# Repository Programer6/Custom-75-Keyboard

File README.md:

# Wireless 75% Keyboard

This is the documentation for  designed completely from scratch.

For the firmware, I chose ZMK. Since this is a wireless build using the `nice!nano`, ZMK's powerful features and Bluetooth support were a perfect fit, even if it meant a steeper learning curve than like KMK which I have used before.

# Hardware Features
- 74-key, 70% layout with a function row.
- Wireless Bluetooth connectivity via a `nice!nano` microcontroller.
- `MCP23017` I/O expander to simplify wiring and save controller pins.
- 1x Rotary Encoder for volume or scrolling.
- Onboard potentiometer for screen brightness adjustment.
- Powered by a LiPo battery.

## Images

| Schematic  |
| :---: |
| |
|  |

| PCB Layout |
| :---: |
|  |

| 3D Case Design |
| :---: |
|  |

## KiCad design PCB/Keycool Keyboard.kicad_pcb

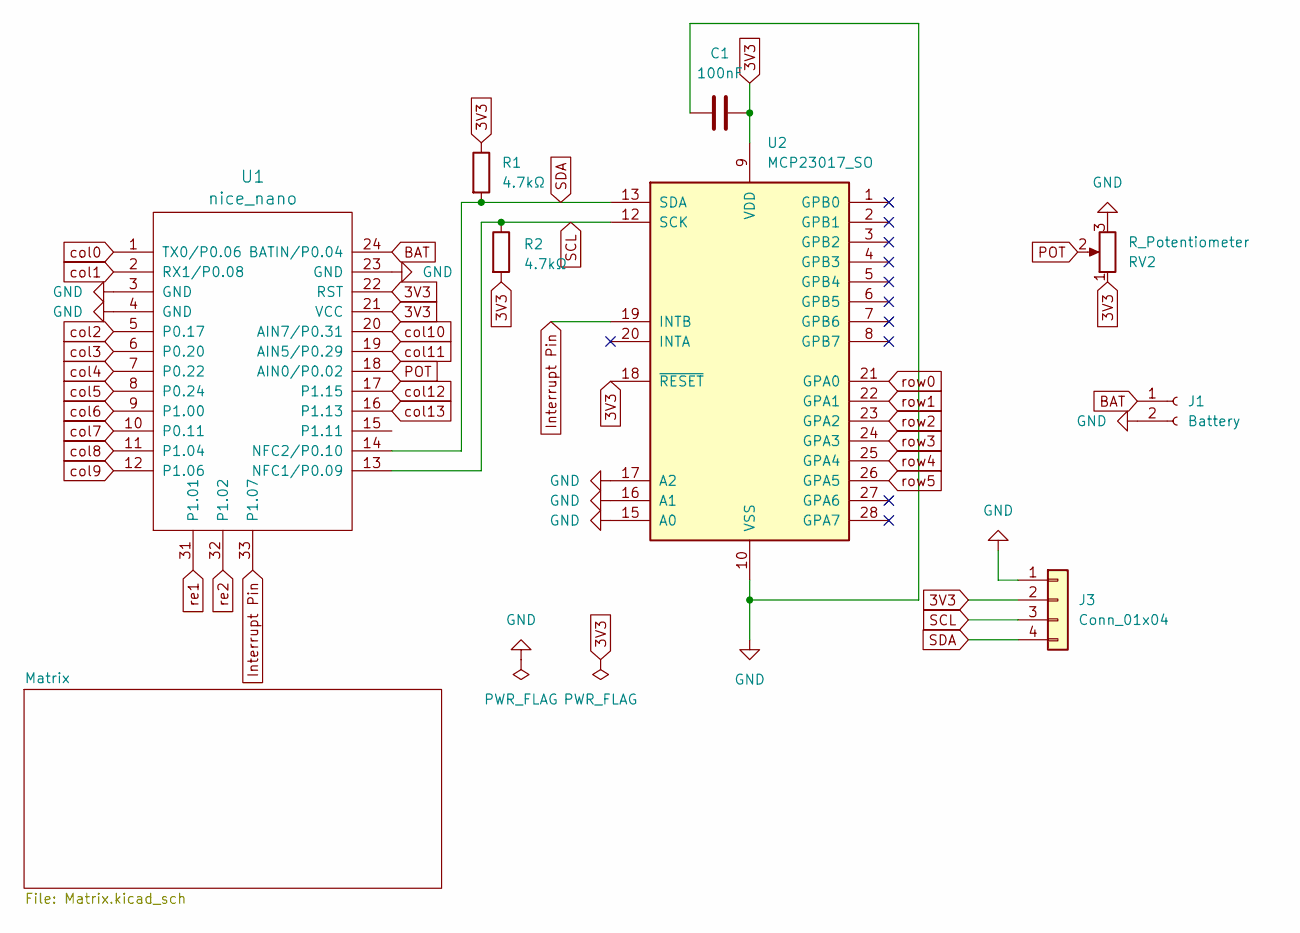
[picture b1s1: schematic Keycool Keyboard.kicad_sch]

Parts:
C1: 100nF; C_0805_2012Metric_Pad1.18x1.45mm_HandSolder
J1: Battery; JST_XH_B2B-XH-AM_1x02_P2.50mm_Vertical
J3: Conn_01x04; SSD1306-0.91-OLED-4pin-128x32
R1, R2: 4.7kΩ; R_0805_2012Metric_Pad1.20x1.40mm_HandSolder
RV2: R_Potentiometer; Sliding_Pot
U1: nice_nano
U2: MCP23017_SO; SOIC-28W_7.5x17.9mm_P1.27mm

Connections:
3V3: C1.2, J3.2, R1.1, R2.2, RV2.1, U1.21 (VCC), U1.22 (RST), U2.9 (VDD), U2.18 (~RESET)
BAT: J1.1, U1.24 (BATIN/P0.04)
GND: C1.1, J1.2, J3.1, RV2.3, U1.3 (GND), U1.4 (GND), U1.23 (GND), U2.10 (VSS), U2.15 (A0), U2.16 (A1), U2.17 (A2); also elsewhere on the board
Interrupt Pin: U1.33 (P1.07), U2.19 (INTB)
POT: RV2.2, U1.18 (AIN0/P0.02)
SCL: J3.3, R2.1, U1.13 (NFC1/P0.09), U2.12 (SCK)
SDA: J3.4, R1.2, U1.14 (NFC2/P0.10), U2.13 (SDA)
col0: U1.1 (TX0/P0.06); also elsewhere on the board
col1: U1.2 (RX1/P0.08); also elsewhere on the board
col2: U1.5 (P0.17); also elsewhere on the board
col3: U1.6 (P0.20); also elsewhere on the board
col4: U1.7 (P0.22); also elsewhere on the board
col5: U1.8 (P0.24); also elsewhere on the board
col6: U1.9 (P1.00); also elsewhere on the board
col7: U1.10 (P0.11); also elsewhere on the board
col8: U1.11 (P1.04); also elsewhere on the board
col9: U1.12 (P1.06); also elsewhere on the board
col10: U1.20 (AIN7/P0.31); also elsewhere on the board
col11: U1.19 (AIN5/P0.29); also elsewhere on the board
col12: U1.17 (P1.15); also elsewhere on the board
col13: U1.16 (P1.13); also elsewhere on the board
re1: U1.31 (P1.01); also elsewhere on the board
re2: U1.32 (P1.02); also elsewhere on the board
row0: U2.21 (GPA0); also elsewhere on the board
row1: U2.22 (GPA1); also elsewhere on the board
row2: U2.23 (GPA2); also elsewhere on the board
row3: U2.24 (GPA3); also elsewhere on the board
row4: U2.25 (GPA4); also elsewhere on the board
row5: U2.26 (GPA5); also elsewhere on the board

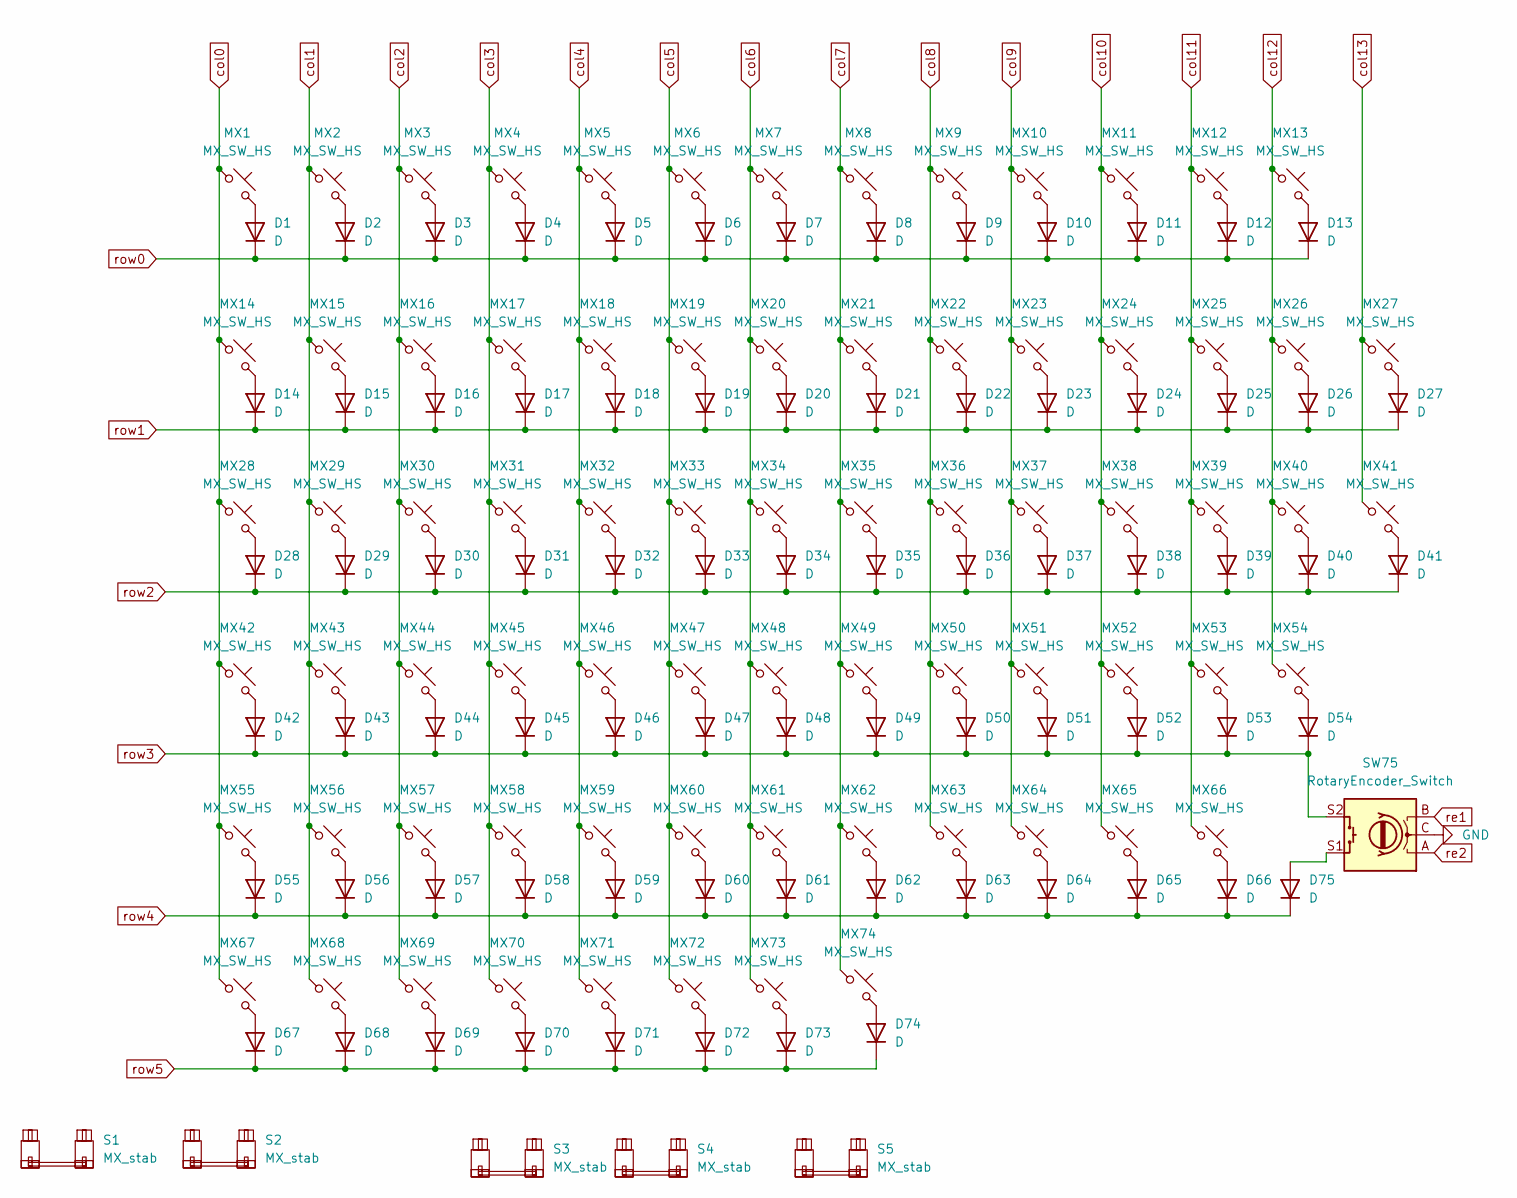
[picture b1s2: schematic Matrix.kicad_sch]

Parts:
D1, D2, D3, D4, D5, D6, D7, D8, D9, D10, D11, D12, D13, D14, D15, D16, D17, D18, D19, D20, D21, D22, D23, D24, D25, D26, D27, D28, D29, D30, D31, D32, D33, D34, D35, D36, D37, D38, D39, D40, D41, D42, D43, D44, D45, D46, D47, D48, D49, D50, D51, D52, D53, D54, D55, D56, D57, D58, D59, D60, D61, D62, D63, D64, D65, D66, D67, D68, D69, D70, D71, D72, D73, D74, D75: D; D_SOD-123
MX1, MX2, MX3, MX4, MX5, MX6, MX7, MX8, MX9, MX10, MX11, MX12, MX13, MX14, MX15, MX16, MX17, MX18, MX19, MX20, MX21, MX22, MX23, MX24, MX25, MX26, MX27, MX29, MX30, MX31, MX32, MX33, MX34, MX35, MX36, MX37, MX38, MX39, MX40, MX43, MX44, MX45, MX46, MX47, MX48, MX49, MX50, MX51, MX52, MX53, MX54, MX55, MX56, MX57, MX58, MX59, MX60, MX61, MX62, MX63, MX64, MX65, MX66, MX70: MX_SW_HS; SW_MX_HS_CPG151101S11_1u
MX28, MX41: MX_SW_HS; SW_MX_HS_CPG151101S11_1.5u
MX42: MX_SW_HS; SW_MX_HS_CPG151101S11_1.75u
MX67, MX68, MX69, MX71, MX72, MX73, MX74: MX_SW_HS; SW_MX_HS_CPG151101S11_1.25u
S1: MX_stab; STAB_MX_P_6.25u
S2: MX_stab; STAB_MX_P_2u
S3, S4: MX_stab; STAB_MX_P_2.25u
S5: MX_stab; STAB_MX_P_2.75u
SW75: RotaryEncoder_Switch; RotaryEncoder_Alps_EC11E-Switch_Vertical_H20mm_CircularMoun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

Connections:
GND: SW75.C; also elsewhere on the board
unnamed: D1.2 (A), MX1.2
unnamed: D2.2 (A), MX2.2
unnamed: D3.2 (A), MX3.2
unnamed: D4.2 (A), MX4.2
unnamed: D5.2 (A), MX5.2
unnamed: D6.2 (A), MX6.2
unnamed: D7.2 (A), MX7.2
unnamed: D8.2 (A), MX8.2
unnamed: D9.2 (A), MX9.2
unnamed: D10.2 (A), MX10.2
unnamed: D11.2 (A), MX11.2
unnamed: D12.2 (A), MX12.2
unnamed: D13.2 (A), MX13.2
unnamed: D14.2 (A), MX14.2
unnamed: D15.2 (A), MX15.2
unnamed: D16.2 (A), MX16.2
unnamed: D17.2 (A), MX17.2
unnamed: D18.2 (A), MX18.2
unnamed: D19.2 (A), MX19.2
unnamed: D20.2 (A), MX20.2
unnamed: D21.2 (A), MX21.2
unnamed: D22.2 (A), MX22.2
unnamed: D23.2 (A), MX23.2
unnamed: D24.2 (A), MX24.2
unnamed: D25.2 (A), MX25.2
unnamed: D26.2 (A), MX26.2
unnamed: D27.2 (A), MX27.2
unnamed: D28.2 (A), MX28.2
unnamed: D29.2 (A), MX29.2
unnamed: D30.2 (A), MX30.2
unnamed: D31.2 (A), MX31.2
unnamed: D32.2 (A), MX32.2
unnamed: D33.2 (A), MX33.2
unnamed: D34.2 (A), MX34.2
unnamed: D35.2 (A), MX35.2
unnamed: D36.2 (A), MX36.2
unnamed: D37.2 (A), MX37.2
unnamed: D38.2 (A), MX38.2
unnamed: D39.2 (A), MX39.2
unnamed: D40.2 (A), MX40.2
unnamed: D41.2 (A), MX41.2
unnamed: D42.2 (A), MX42.2
unnamed: D43.2 (A), MX43.2
unnamed: D44.2 (A), MX44.2
unnamed: D45.2 (A), MX45.2
unnamed: D46.2 (A), MX46.2
unnamed: D47.2 (A), MX47.2
unnamed: D48.2 (A), MX48.2
unnamed: D49.2 (A), MX49.2
unnamed: D50.2 (A), MX50.2
unnamed: D51.2 (A), MX51.2
unnamed: D52.2 (A), MX52.2
unnamed: D53.2 (A), MX53.2
unnamed: D54.2 (A), MX54.2
unnamed: D55.2 (A), MX55.2
unnamed: D56.2 (A), MX56.2
unnamed: D57.2 (A), MX57.2
unnamed: D58.2 (A), MX58.2
unnamed: D59.2 (A), MX59.2
unnamed: D60.2 (A), MX60.2
unnamed: D61.2 (A), MX61.2
unnamed: D62.2 (A), MX62.2
unnamed: D63.2 (A), MX63.2
unnamed: D64.2 (A), MX64.2
unnamed: D65.2 (A), MX65.2
unnamed: D66.2 (A), MX66.2
unnamed: D67.2 (A), MX67.2
unnamed: D68.2 (A), MX68.2
unnamed: D69.2 (A), MX69.2
unnamed: D70.2 (A), MX70.2
unnamed: D71.2 (A), MX71.2
unnamed: D72.2 (A), MX72.2
unnamed: D73.2 (A), MX73.2
unnamed: D74.2 (A), MX74.2
unnamed: D75.2 (A), SW75.S1
col0: MX1.1, MX14.1, MX28.1, MX42.1, MX55.1, MX67.1; also elsewhere on the board
col1: MX2.1, MX15.1, MX29.1, MX43.1, MX56.1, MX68.1; also elsewhere on the board
col2: MX3.1, MX16.1, MX30.1, MX44.1, MX57.1, MX69.1; also elsewhere on the board
col3: MX4.1, MX17.1, MX31.1, MX45.1, MX58.1, MX70.1; also elsewhere on the board
col4: MX5.1, MX18.1, MX32.1, MX46.1, MX59.1, MX71.1; also elsewhere on the board
col5: MX6.1, MX19.1, MX33.1, MX47.1, MX60.1, MX72.1; also elsewhere on the board
col6: MX7.1, MX20.1, MX34.1, MX48.1, MX61.1, MX73.1; also elsewhere on the board
col7: MX8.1, MX21.1, MX35.1, MX49.1, MX62.1, MX74.1; also elsewhere on the board
col8: MX9.1, MX22.1, MX36.1, MX50.1, MX63.1; also elsewhere on the board
col9: MX10.1, MX23.1, MX37.1, MX51.1, MX64.1; also elsewhere on the board
col10: MX11.1, MX24.1, MX38.1, MX52.1, MX65.1; also elsewhere on the board
col11: MX12.1, MX25.1, MX39.1, MX53.1, MX66.1; also elsewhere on the board
col12: MX13.1, MX26.1, MX40.1, MX54.1; also elsewhere on the board
col13: MX27.1, MX41.1; also elsewhere on the board
re1: SW75.B; also elsewhere on the board
re2: SW75.A; also elsewhere on the board
row0: D1.1 (K), D2.1 (K), D3.1 (K), D4.1 (K), D5.1 (K), D6.1 (K), D7.1 (K), D8.1 (K), D9.1 (K), D10.1 (K), D11.1 (K), D12.1 (K), D13.1 (K); also elsewhere on the board
row1: D14.1 (K), D15.1 (K), D16.1 (K), D17.1 (K), D18.1 (K), D19.1 (K), D20.1 (K), D21.1 (K), D22.1 (K), D23.1 (K), D24.1 (K), D25.1 (K), D26.1 (K), D27.1 (K); also elsewhere on the board
row2: D28.1 (K), D29.1 (K), D30.1 (K), D31.1 (K), D32.1 (K), D33.1 (K), D34.1 (K), D35.1 (K), D36.1 (K), D37.1 (K), D38.1 (K), D39.1 (K), D40.1 (K), D41.1 (K); also elsewhere on the board
row3: D42.1 (K), D43.1 (K), D44.1 (K), D45.1 (K), D46.1 (K), D47.1 (K), D48.1 (K), D49.1 (K), D50.1 (K), D51.1 (K), D52.1 (K), D53.1 (K), D54.1 (K), SW75.S2; also elsewhere on the board
row4: D55.1 (K), D56.1 (K), D57.1 (K), D58.1 (K), D59.1 (K), D60.1 (K), D61.1 (K), D62.1 (K), D63.1 (K), D64.1 (K), D65.1 (K), D66.1 (K), D75.1 (K); also elsewhere on the board
row5: D67.1 (K), D68.1 (K), D69.1 (K), D70.1 (K), D71.1 (K), D72.1 (K), D73.1 (K), D74.1 (K); also elsewhere on the board

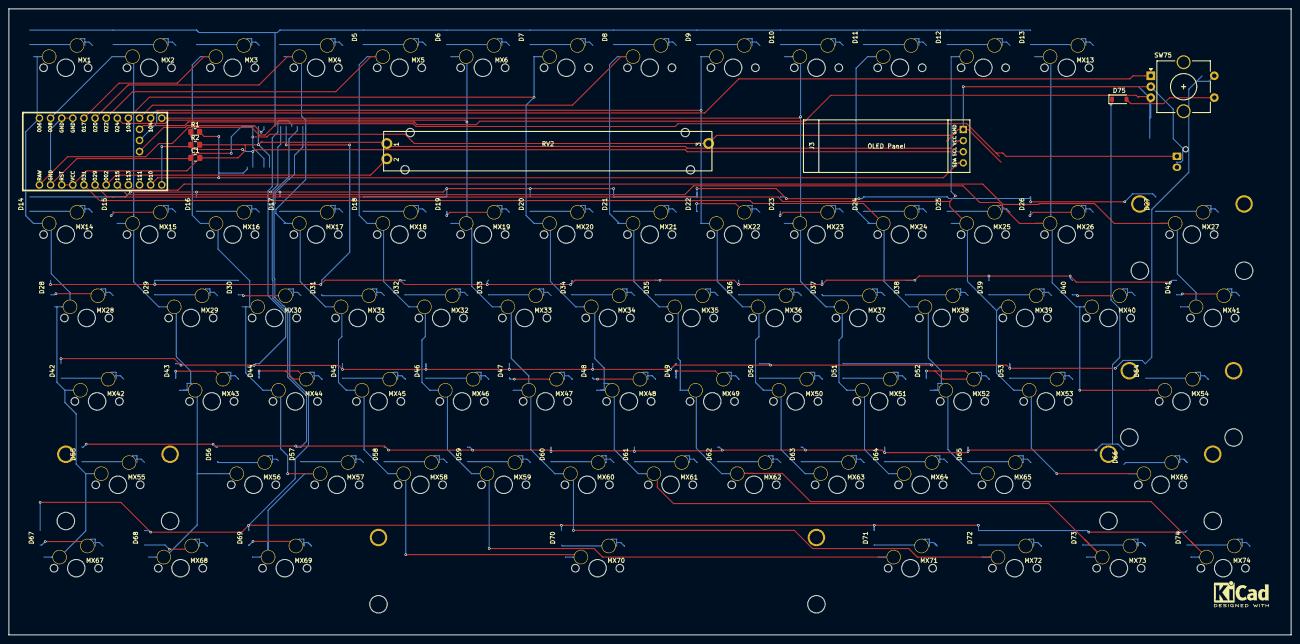
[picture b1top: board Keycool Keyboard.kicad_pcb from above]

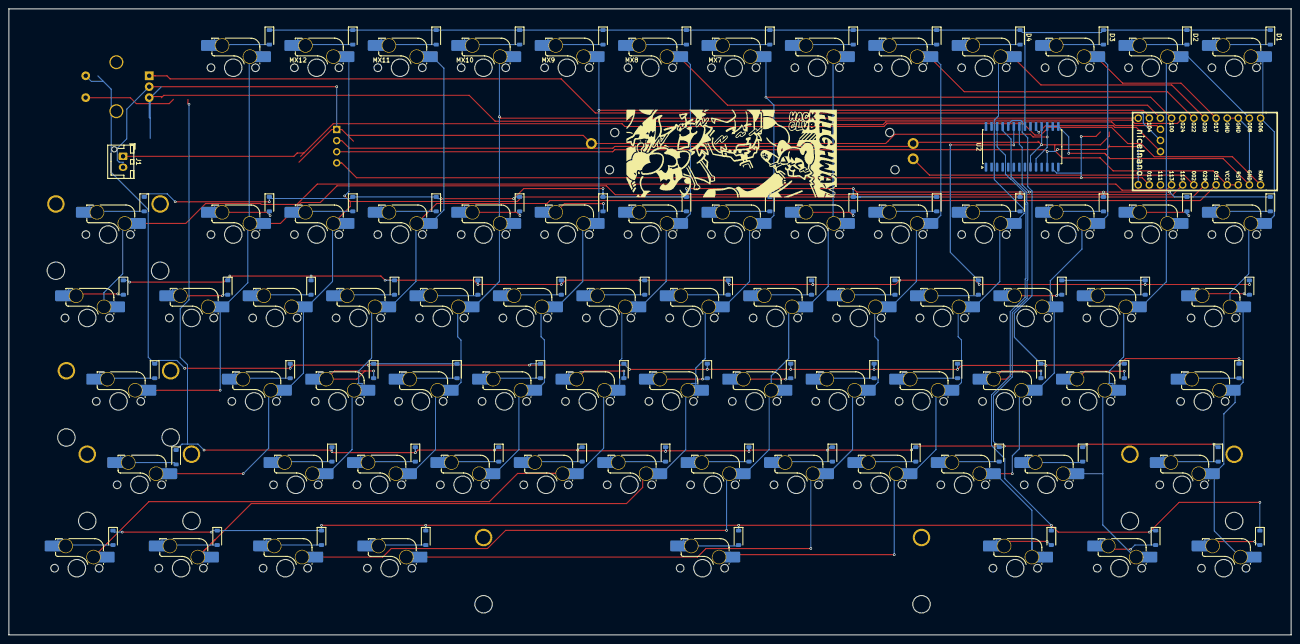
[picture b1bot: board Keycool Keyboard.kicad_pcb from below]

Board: 2 copper layers, 292.9 x 143.0 mm, 163 parts (151 on the bottom side), 104 nets.

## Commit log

2025-07-30 Create test
